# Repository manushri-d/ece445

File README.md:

# Team 41 FA 2024 ECE 445 Digital Lab Notebook

This repo is used for our Senior Design class where we put all of our updates for the semester!

Check [this link](https://courses.grainger.illinois.edu/ece445/projects.asp) for more information on our project (as well as some other projects!)

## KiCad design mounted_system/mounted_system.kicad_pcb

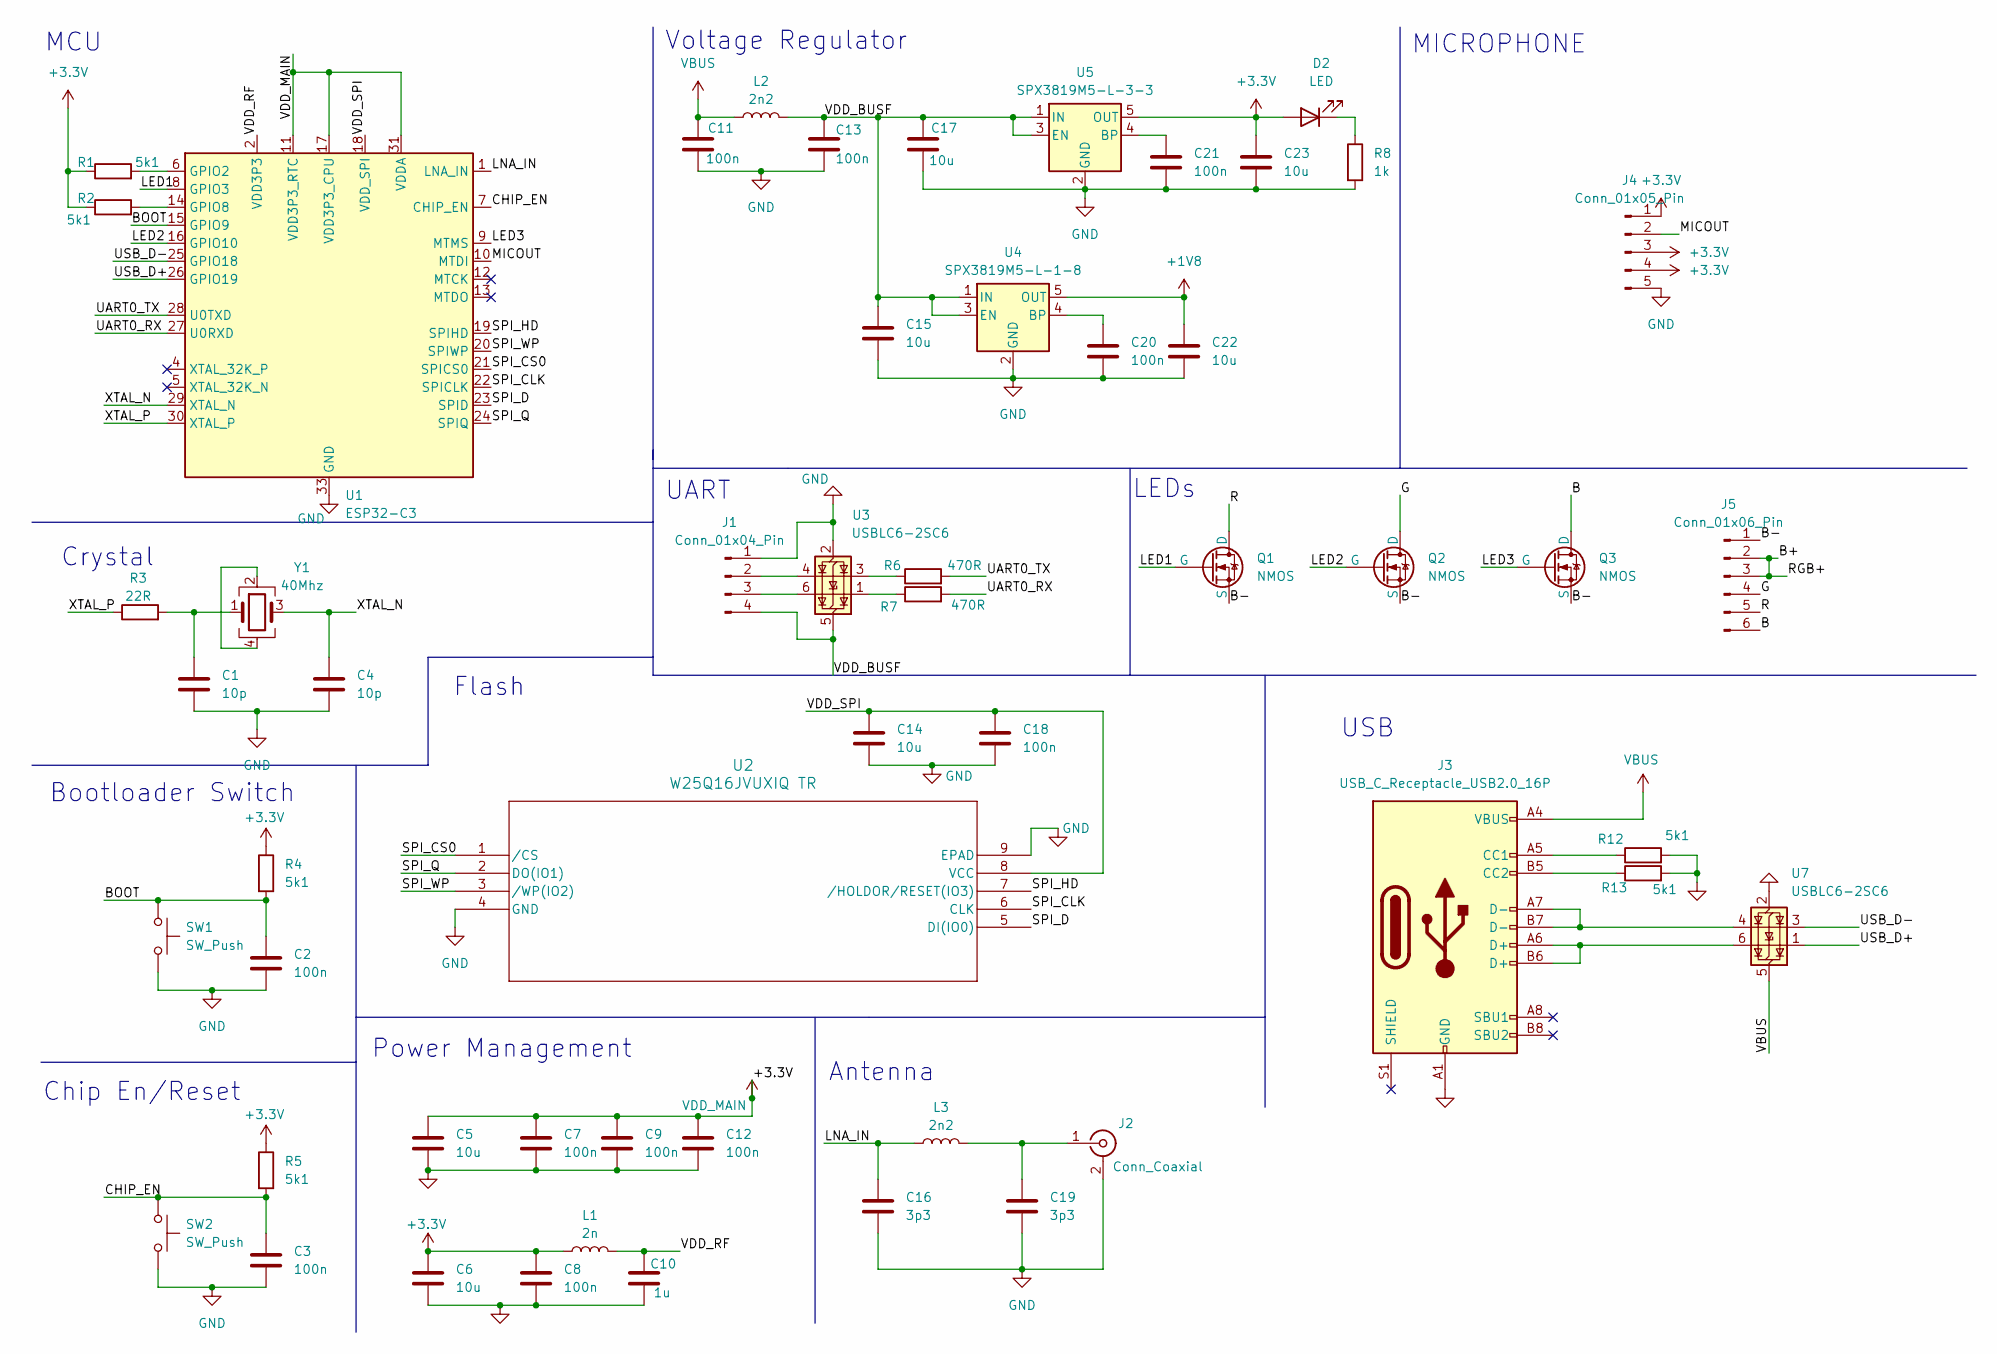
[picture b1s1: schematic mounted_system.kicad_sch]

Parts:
C1, C4: 10p; C_0805_2012Metric_Pad1.18x1.45mm_HandSolder
C2, C3, C7, C8, C9, C11, C12, C13, C18, C20, C21: 100n; C_0805_2012Metric_Pad1.18x1.45mm_HandSolder
C5, C6, C14, C15, C17, C22, C23: 10u; C_0805_2012Metric_Pad1.18x1.45mm_HandSolder
C10: 1u; C_0805_2012Metric_Pad1.18x1.45mm_HandSolder
C16, C19: 3p3; C_0805_2012Metric_Pad1.18x1.45mm_HandSolder
D2: LED; LED_0805_2012Metric_Pad1.15x1.40mm_HandSolder
J1: Conn_01x04_Pin; PinSocket_1x04_P2.00mm_Vertical
J2: Conn_Coaxial; MMCX_Molex_73415-1471_Vertical
J3: USB_C_Receptacle_USB2.0_16P; USB_C_Receptacle_XKB_U262-16XN-4BVC11
J4: Conn_01x05_Pin; PinSocket_1x05_P2.00mm_Vertical_SMD_Pin1Right
J5: Conn_01x06_Pin; PinSocket_1x06_P2.00mm_Vertical_SMD_Pin1Right
L1: 2n; L_0805_2012Metric_Pad1.15x1.40mm_HandSolder
L2, L3: 2n2; L_0805_2012Metric_Pad1.15x1.40mm_HandSolder
Q1, Q2, Q3: NMOS; TO-247-3_Vertical
R1, R2, R4, R5, R12, R13: 5k1; R_0805_2012Metric_Pad1.20x1.40mm_HandSolder
R3: 22R; R_0805_2012Metric_Pad1.20x1.40mm_HandSolder
R6, R7: 470R; R_0805_2012Metric_Pad1.20x1.40mm_HandSolder
R8: 1k; R_0805_2012Metric_Pad1.20x1.40mm_HandSolder
SW1, SW2: SW_Push; SW_SPST_PTS645
U1: ESP32-C3; QFN-32-1EP_5x5mm_P0.5mm_EP3.7x3.7mm
U2: W25Q16JVUXIQ TR; USON-8_UX_2x3x0p6_WIN
U3, U7: USBLC6-2SC6; SOT-23-6
U4: SPX3819M5-L-1-8; SOT-23-5
U5: SPX3819M5-L-3-3; SOT-23-5
Y1: 40Mhz; Crystal_SMD_EuroQuartz_MQ-4Pin_7.0x5.0mm_HandSoldering

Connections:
+1V8: C22.1, U4.5 (OUT)
+3.3V: C5.1, C6.1, C7.1, C8.1, C9.1, C12.1, C23.1, D2.2 (A), J4.1, J4.3, J4.4, L1.1, R1.1, R2.1, R4.1, R5.1, U1.11 (VDD3P3_RTC), U1.17 (VDD3P3_CPU), U1.31 (VDDA), U1.32 (VDDA), U5.5 (OUT)
/B: J5.6, Q3.1 (D)
/B+: J5.2, J5.3
/B-: J5.1, Q1.3 (S), Q2.3 (S), Q3.3 (S)
/BOOT: C2.1, R4.2, SW1.1, U1.15 (GPIO9)
/CHIP_EN: C3.1, R5.2, SW2.1, U1.7 (CHIP_EN)
/G: J5.4, Q2.1 (D)
/LED1: Q1.2 (G), U1.8 (GPIO3)
/LED2: Q2.2 (G), U1.16 (GPIO10)
/LED3: Q3.2 (G), U1.9 (MTMS)
/LNA_IN: C16.1, L3.1, U1.1 (LNA_IN)
/MICOUT: J4.2, U1.10 (MTDI)
/R: J5.5, Q1.1 (D)
/SPI_CLK: U1.22 (SPICLK), U2.6 (CLK)
/SPI_CS0: U1.21 (SPICS0), U2.1 (/CS)
/SPI_D: U1.23 (SPID), U2.5 (DI(IO0))
/SPI_HD: U1.19 (SPIHD), U2.7 (/HOLDOR/RESET(IO3))
/SPI_Q: U1.24 (SPIQ), U2.2 (DO(IO1))
/SPI_WP: U1.20 (SPIWP), U2.3 (/WP(IO2))
/UART0_RX: R7.2, U1.27 (U0RXD)
/UART0_TX: R6.2, U1.28 (U0TXD)
/USB_D+: U1.26 (GPIO19), U7.1 (I/O1)
/USB_D-: U1.25 (GPIO18), U7.3 (I/O2)
/VDD_BUSF: C13.1, C15.1, C17.1, J1.4, L2.2, U3.5 (VBUS), U4.1 (IN), U4.3 (EN), U5.1 (IN), U5.3 (EN)
/VDD_RF: C10.1, L1.2, U1.2 (VDD3P3), U1.3 (VDD3P3)
/VDD_SPI: C14.1, C18.1, U1.18 (VDD_SPI), U2.8 (VCC)
/XTAL_N: C4.1, U1.29 (XTAL_N), Y1.3
/XTAL_P: R3.1, U1.30 (XTAL_P)
GND: C1.2, C2.2, C3.2, C4.2, C5.2, C6.2, C7.2, C8.2, C9.2, C10.2, C11.2, C12.2, C13.2, C14.2, C15.2, C16.2, C17.2, C18.2, C19.2, C20.2, C21.2, C22.2, C23.2, J1.1, J2.2 (Ext), J3.A1 (GND), J3.A12 (GND), J3.B1 (GND), J3.B12 (GND), J4.5, R8.2, R12.2, R13.2, SW1.2, SW2.2, U1.33 (GND), U2.4 (GND), U2.9 (EPAD), U3.2 (GND), U4.2 (GND), U5.2 (GND), U7.2 (GND)
unnamed: C1.1, R3.2, Y1.1
unnamed: D2.1 (K), R8.1
unnamed: J1.2, U3.4 (I/O2)
unnamed: J1.3, U3.6 (I/O1)
unnamed: C19.1, J2.1 (In), L3.2
unnamed: J3.A5 (CC1), R12.1
unnamed: J3.B5 (CC2), R13.1
unnamed: J3.A6 (D+), J3.B6 (D+), U7.6 (I/O1)
unnamed: J3.A7 (D-), J3.B7 (D-), U7.4 (I/O2)
unnamed: R6.1, U3.3 (I/O2)
unnamed: R7.1, U3.1 (I/O1)
unnamed: R1.2, U1.6 (GPIO2)
unnamed: R2.2, U1.14 (GPIO8)
unnamed: C20.1, U4.4 (BP)
unnamed: C21.1, U5.4 (BP)
unnamed: Y1.2, Y1.4
VBUS: C11.1, J3.A4 (VBUS), J3.A9 (VBUS), J3.B4 (VBUS), J3.B9 (VBUS), L2.1, U7.5 (VBUS)

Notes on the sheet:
USB
UART
MCU
Chip En/Reset
Voltage Regulator
Bootloader Switch
MICROPHONE
Crystal
Antenna
Power Management
LEDs
Flash

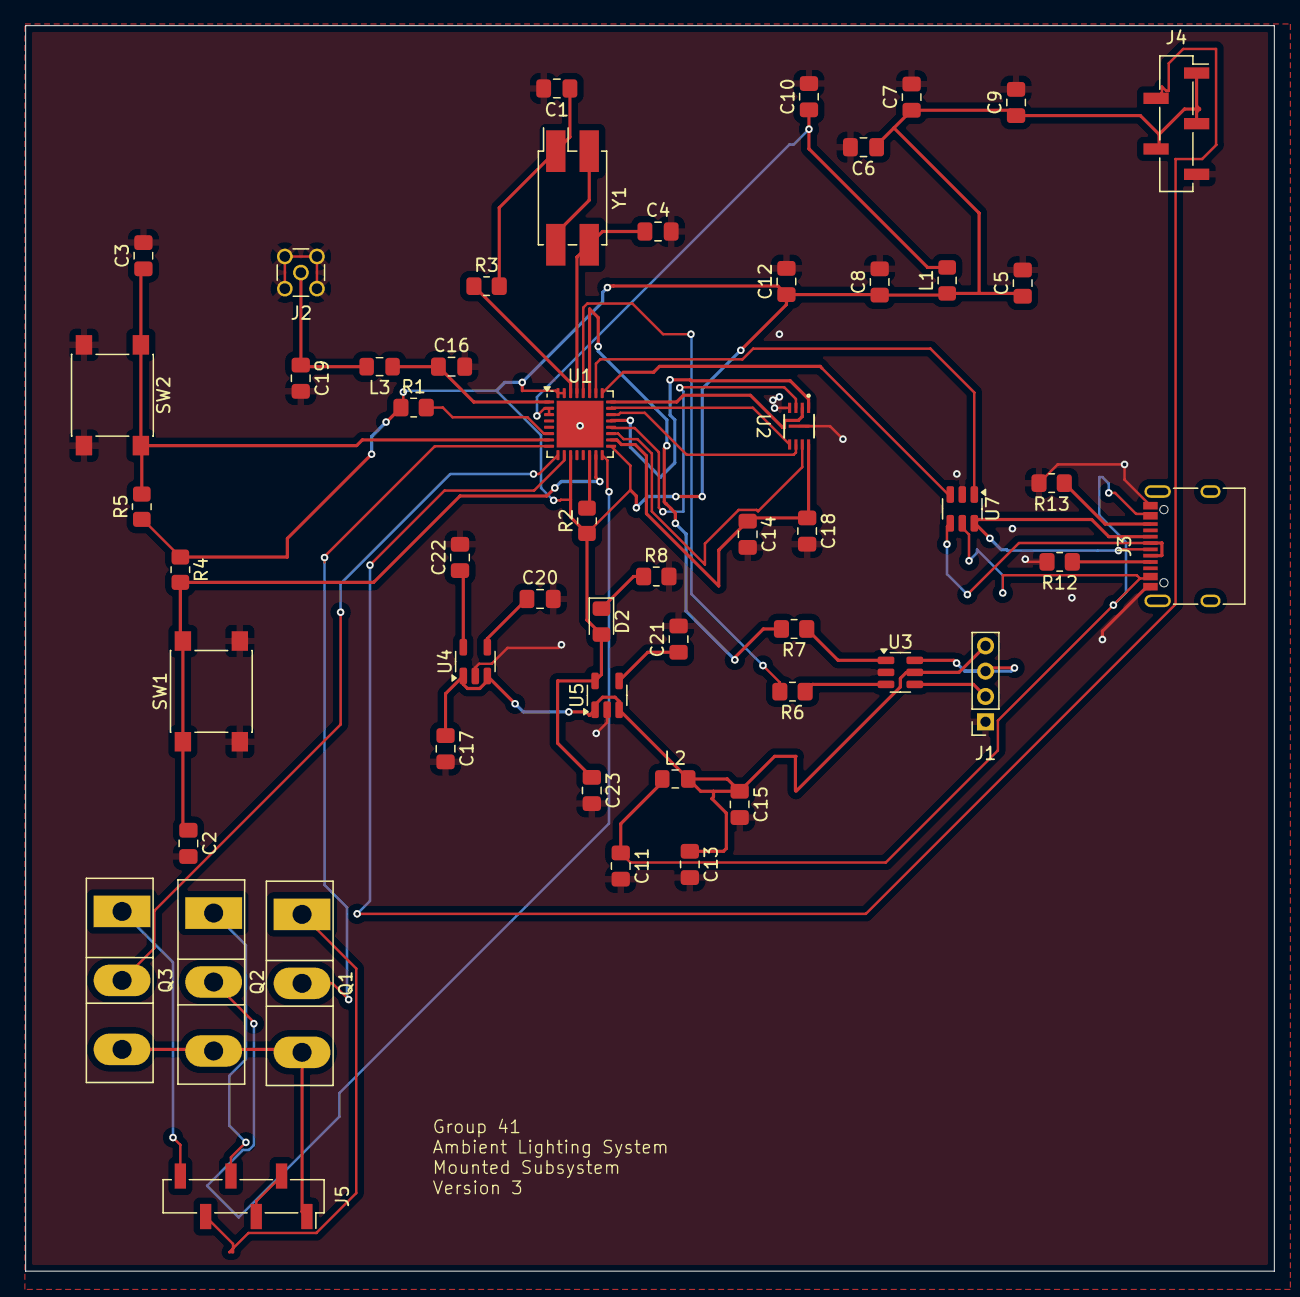
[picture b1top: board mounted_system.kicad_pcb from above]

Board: 2 copper layers, 98.7 x 98.4 mm, 54 parts (0 on the bottom side), 47 nets.

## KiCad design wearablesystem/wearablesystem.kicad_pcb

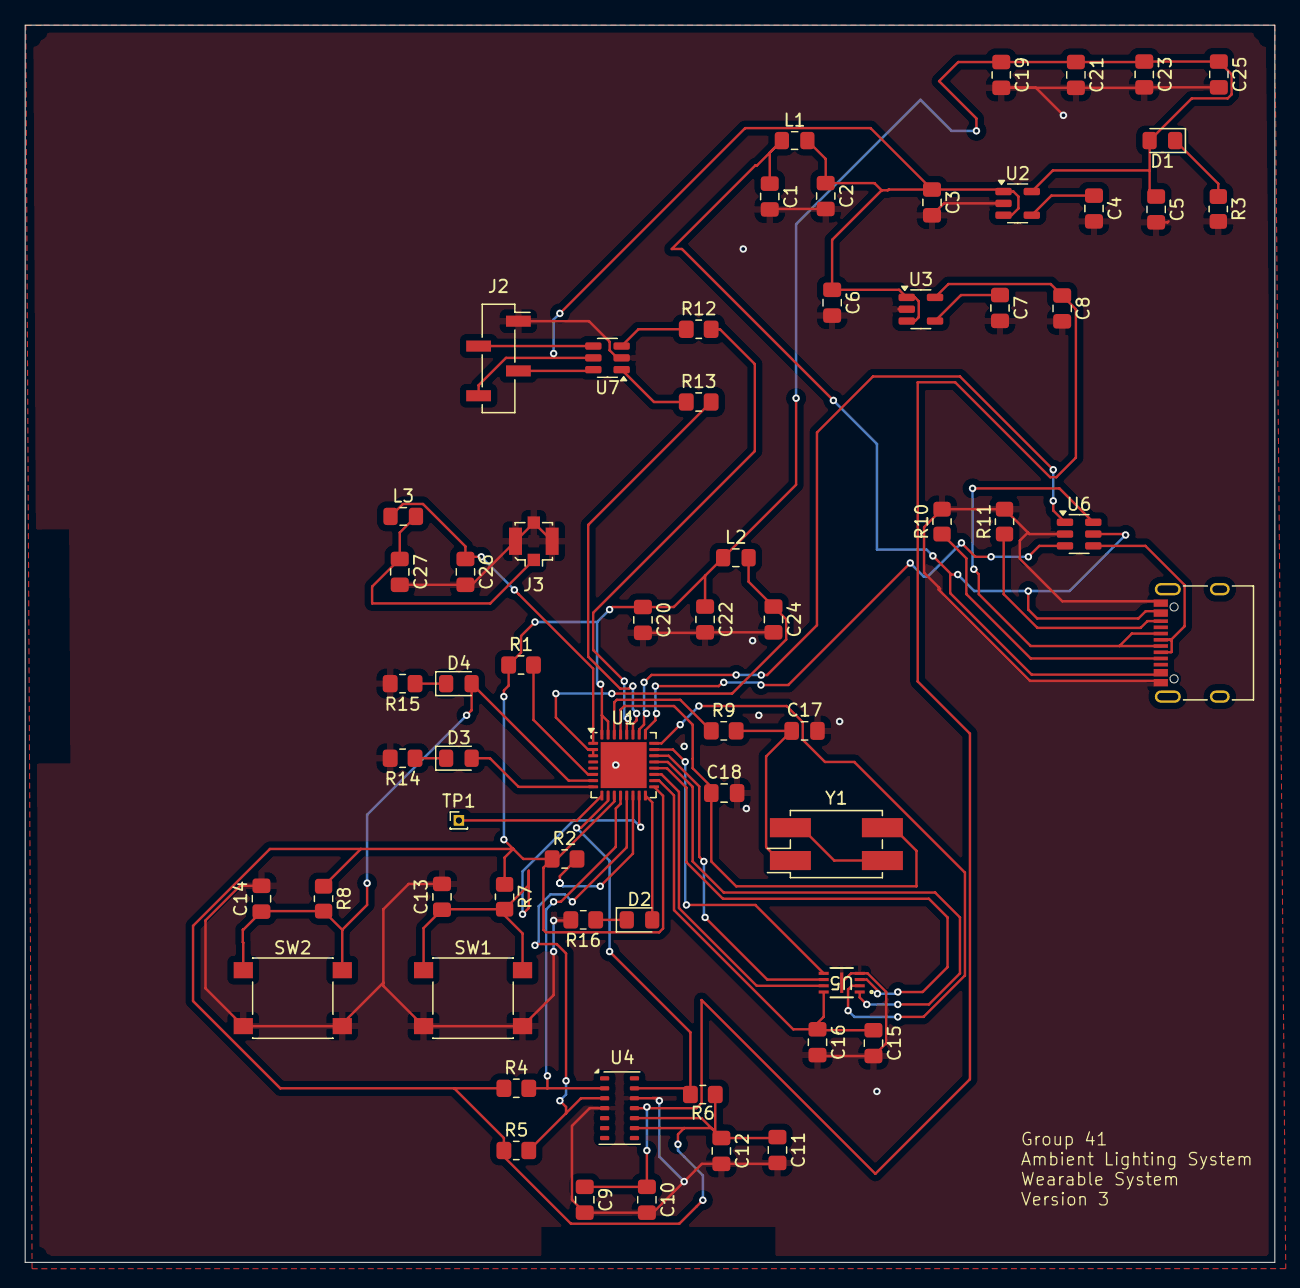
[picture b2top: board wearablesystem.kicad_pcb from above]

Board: 2 copper layers, 100.5 x 99.5 mm, 64 parts (0 on the bottom side), 47 nets.

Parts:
C1, C2, C4, C7, C9, C12, C13, C14, C16, C21, C22, C23, C25: 100n; C_0805_2012Metric_Pad1.18x1.45mm_HandSolder
C3, C5, C6, C8, C10, C15, C19, C20: 10u; C_0805_2012Metric_Pad1.18x1.45mm_HandSolder
C11, C24: 1u; C_0805_2012Metric_Pad1.18x1.45mm_HandSolder
C17, C18: 10p; C_0805_2012Metric_Pad1.18x1.45mm_HandSolder
C26, C27: 3p3; C_0805_2012Metric_Pad1.18x1.45mm_HandSolder
D1, D2, D3, D4: LED; LED_0805_2012Metric_Pad1.15x1.40mm_HandSolder
J1: USB_C_Receptacle_USB2.0_16P; USB_C_Receptacle_XKB_U262-16XN-4BVC11
J2: Conn_01x04_Pin; PinSocket_1x04_P2.00mm_Vertical_SMD_Pin1Right
J3: Conn_Coaxial; U.FL_Molex_MCRF_73412-0110_Vertical
L1, L3: 2n2; L_0805_2012Metric_Pad1.15x1.40mm_HandSolder
L2: 2n; L_0805_2012Metric_Pad1.15x1.40mm_HandSolder
R1, R2, R7, R8, R10, R11: 5k1; R_0805_2012Metric_Pad1.20x1.40mm_HandSolder
R3, R14, R15, R16: 1k; R_0805_2012Metric_Pad1.20x1.40mm_HandSolder
R4, R5, R6: 1k5; R_0805_2012Metric_Pad1.20x1.40mm_HandSolder
R9: 22R; R_0805_2012Metric_Pad1.20x1.40mm_HandSolder
R12, R13: 470R; R_0805_2012Metric_Pad1.20x1.40mm_HandSolder
SW1, SW2: SW_Push; SW_SPST_PTS645
TP1: TestPoint; PinHeader_1x01_P1.00mm_Vertical
U1: ESP32-C3; QFN-32-1EP_5x5mm_P0.5mm_EP3.7x3.7mm
U2: SPX3819M5-L-3-3; SOT-23-5
U3: SPX3819M5-L-1-8; SOT-23-5
U4: MAX30102; Maxim_OLGA-14_3.3x5.6mm_P0.8mm
U5: W25Q16JVUXIQ TR; USON-8_UX_2x3x0p6_WIN
U6, U7: USBLC6-2SC6; SOT-23-6
Y1: 40Mhz; Crystal_SMD_EuroQuartz_MQ-4Pin_7.0x5.0mm_HandSoldering

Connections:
+1V8: C8.1, C9.1, C10.1, U3.5 (OUT), U4.11 (VDD)
+3.3V: C5.1, C11.1, C12.1, C19.1, C20.1, C21.1, C22.1, C23.1, C25.1, D1.2 (A), L2.1, R1.1, R2.1, R4.1, R5.1, R6.1, R7.1, R8.1, U1.11 (VDD3P3_RTC), U1.17 (VDD3P3_CPU), U1.31 (VDDA), U1.32 (VDDA), U2.5 (OUT), U4.9 (VLED+), U4.10 (VLED+)
/BOOT: C13.1, R7.2, SW1.1, U1.15 (GPIO9)
/CHIP_EN: C14.1, D4.2 (A), R8.2, SW2.1, U1.7 (CHIP_EN)
/INT: R6.2, U1.10 (MTDI), U4.13 (~INT)
/LED1: D3.2 (A), U1.8 (GPIO3)
/LED2: D2.2 (A), U1.16 (GPIO10)
/LNA_IN: C26.1, L3.1, U1.1 (LNA_IN)
/MTMS: TP1.1, U1.9 (MTMS)
/SCL: R4.2, U1.12 (MTCK), U4.2 (SCL)
/SDA: R5.2, U1.13 (MTDO), U4.3 (SDA)
/SPI_CLK: U1.22 (SPICLK), U5.6 (CLK)
/SPI_CS0: U1.21 (SPICS0), U5.1 (/CS)
/SPI_D: U1.23 (SPID), U5.5 (DI(IO0))
/SPI_HD: U1.19 (SPIHD), U5.7 (/HOLDOR/RESET(IO3))
/SPI_Q: U1.24 (SPIQ), U5.2 (DO(IO1))
/SPI_WP: U1.20 (SPIWP), U5.3 (/WP(IO2))
/UART0_RX: R13.2, U1.27 (U0RXD)
/UART0_TX: R12.2, U1.28 (U0TXD)
/USB_D+: U1.26 (GPIO19), U6.1 (I/O1)
/USB_D-: U1.25 (GPIO18), U6.3 (I/O2)
/VDD_BUSF: C2.1, C3.1, C6.1, J2.4, L1.2, U2.1 (IN), U2.3 (EN), U3.1 (IN), U3.3 (EN), U7.5 (VBUS)
/VDD_RF: C24.1, L2.2, U1.2 (VDD3P3), U1.3 (VDD3P3)
/VDD_SPI: C15.1, C16.1, U1.18 (VDD_SPI), U5.8 (VCC)
/XTAL_N: C18.1, U1.29 (XTAL_N), Y1.3
/XTAL_P: R9.1, U1.30 (XTAL_P)
GND: C1.2, C2.2, C3.2, C4.2, C5.2, C6.2, C7.2, C8.2, C9.2, C10.2, C11.2, C12.2, C13.2, C14.2, C15.2, C16.2, C17.2, C18.2, C19.2, C20.2, C21.2, C22.2, C23.2, C24.2, C25.2, C26.2, C27.2, J1.A1 (GND), J1.A12 (GND), J1.B1 (GND), J1.B12 (GND), J2.1, J3.2 (Ext), R3.2, R10.2, R11.2, R14.2, R15.2, R16.2, SW1.2, SW2.2, U1.33 (GND), U2.2 (GND), U3.2 (GND), U4.4 (PGND), U4.12 (GND), U5.4 (GND), U5.9 (EPAD), U6.2 (GND), U7.2 (GND)
unnamed: C17.1, R9.2, Y1.1
unnamed: D1.1 (K), R3.1
unnamed: D2.1 (K), R16.1
unnamed: D3.1 (K), R14.1
unnamed: D4.1 (K), R15.1
unnamed: J1.A5 (CC1), R10.1
unnamed: J1.B5 (CC2), R11.1
unnamed: J1.A6 (D+), J1.B6 (D+), U6.6 (I/O1)
unnamed: J1.A7 (D-), J1.B7 (D-), U6.4 (I/O2)
unnamed: J2.2, U7.4 (I/O2)
unnamed: J2.3, U7.6 (I/O1)
unnamed: C27.1, J3.1 (In), L3.2
unnamed: R12.1, U7.3 (I/O2)
unnamed: R13.1, U7.1 (I/O1)
unnamed: R1.2, U1.6 (GPIO2)
unnamed: R2.2, U1.14 (GPIO8)
unnamed: C4.1, U2.4 (BP)
unnamed: C7.1, U3.4 (BP)
unnamed: Y1.2, Y1.4
VBUS: C1.1, J1.A4 (VBUS), J1.A9 (VBUS), J1.B4 (VBUS), J1.B9 (VBUS), L1.1, U6.5 (VBUS)

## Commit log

2024-11-06 Adding Mounted Subsystem
2024-11-06 adding wearable system
2024-11-06 Making indiviudal folders
2024-11-06 Adding team contract
2024-11-06 adding design doc
2024-11-12 maybe fixed errors
2024-11-12 added files plus gerber
2024-11-14 adding new files
2024-11-15 fully updated pcb
2024-12-11 adding final report
2024-12-11 adding bambu files
2024-12-11 Adding Files:
2024-12-11 finished
2024-12-11 Adding code
2024-12-11 adding hr code
